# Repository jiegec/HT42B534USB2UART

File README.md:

# HT42B534 USB 2 UART Board

A simple USB to UART board. Designed with KiCad. Manufactured and tested.

## How to use

1. Plug USB to your PC
2. Wire VIO to either V33O(3.3V) or VDD(5V)
3. Connect TX, RX & GND (optionally VIO) to other devices

The voltage of RX/TX should match VIO.

## Bill of Materials

```csv
Reference, Value, Footprint, Datasheet, Product
"U1","HT42B534_8SOP","Package_SO:SOP-8_3.9x4.9mm_P1.27mm","https://www.holtek.com/documents/10179/116711/HT42B534-xv110.pdf","https://item.szlcsc.com/504007.html"
"C1","0.1uF","Capacitor_SMD:C_0603_1608Metric_Pad1.08x0.95mm_HandSolder","~"
"J1","USB_A","Connector_USB:USB_A_CNCTech_1001-011-01101_Horizontal","~","https://item.szlcsc.com/98530.html"
"R2","33","Resistor_SMD:R_0603_1608Metric_Pad0.98x0.95mm_HandSolder","~"
"R1","33","Resistor_SMD:R_0603_1608Metric_Pad0.98x0.95mm_HandSolder","~"
"C6","47pF","Capacitor_SMD:C_0603_1608Metric_Pad1.08x0.95mm_HandSolder","~"
"C7","47pF","Capacitor_SMD:C_0603_1608Metric_Pad1.08x0.95mm_HandSolder","~"
"C3","1uF","Capacitor_SMD:C_0603_1608Metric_Pad1.08x0.95mm_HandSolder","~"
"C2","0.1uF","Capacitor_SMD:C_0603_1608Metric_Pad1.08x0.95mm_HandSolder","~"
"C4","10uF","Capacitor_SMD:C_0603_1608Metric_Pad1.08x0.95mm_HandSolder","~"
"C5","0.1uF","Capacitor_SMD:C_0603_1608Metric_Pad1.08x0.95mm_HandSolder","~"
"R3","330","Resistor_SMD:R_0603_1608Metric_Pad0.98x0.95mm_HandSolder","~"
"D1","LED","Diode_SMD:D_0603_1608Metric_Pad1.05x0.95mm_HandSolder","~"
"J3","Conn_01x03","Connector_PinHeader_2.54mm:PinHeader_1x03_P2.54mm_Vertical","~"
"J2","Conn_01x04","Connector_PinHeader_2.54mm:PinHeader_1x04_P2.54mm_Horizontal","~"
```

## USB Device Info

`lsusb` output:

```shell
$ lsusb
Bus 000 Device 001: ID 04d9:b534 Holtek Semiconductor, Inc. USB TO UART BRIDGE  Serial: 0000
```

System Information:

```
USB TO UART BRIDGE:

  Product ID:	0xb534
  Vendor ID:	0x04d9  (Holtek Semiconductor, Inc.)
  Version:	2.10
  Serial Number:	0000
  Speed:	Up to 12 Mb/s
  Manufacturer:	HOLTEK
  Location ID:	0x00142000 / 12
  Current Available (mA):	500
  Current Required (mA):	100
  Extra Operating Current (mA):	0
```

## License

Copyright 2020-2021 Jiajie Chen

SPDX-License-Identifier: Apache-2.0 WITH SHL-2.1

Licensed under the Solderpad Hardware License v 2.1 (the “License”); you may not use this file except in compliance with the License, or, at your option, the Apache License version 2.0. You may obtain a copy of the License at

https://solderpad.org/licenses/SHL-2.1/

Unless required by applicable law or agreed to in writing, any work distributed under the License is distributed on an “AS IS” BASIS, WITHOUT WARRANTIES OR CONDITIONS OF ANY KIND, either express or implied. See the License for the specific language governing permissions and limitations under the License.

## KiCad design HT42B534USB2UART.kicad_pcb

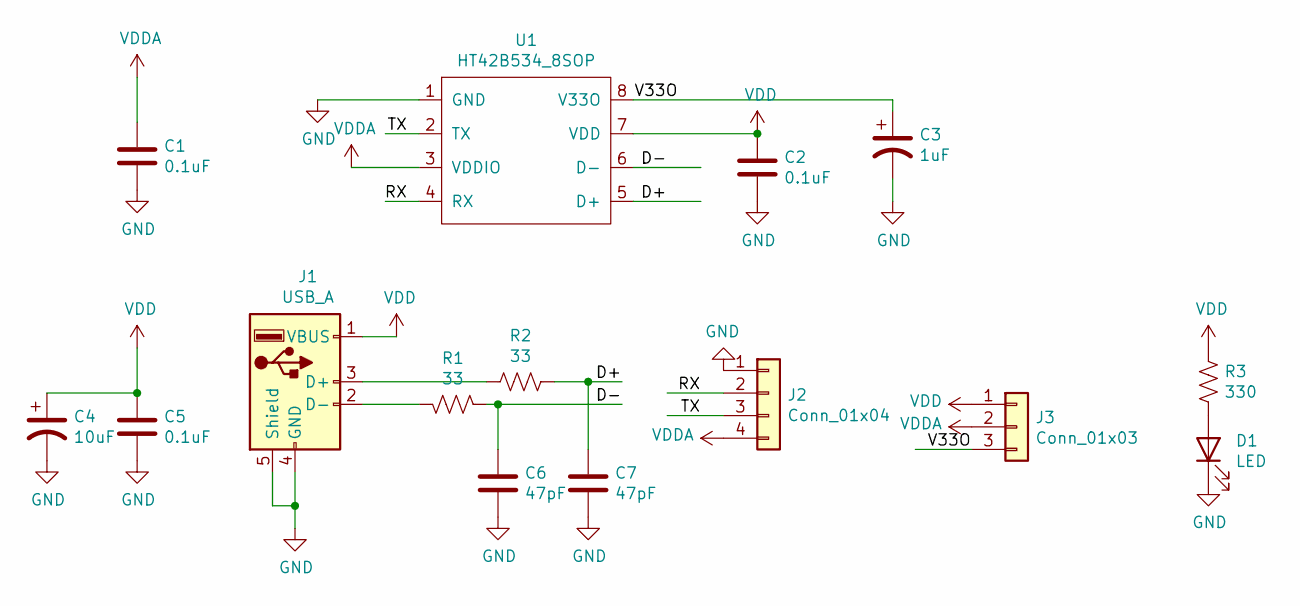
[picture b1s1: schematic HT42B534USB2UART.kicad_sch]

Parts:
C1, C2, C5: 0.1uF; C_0603_1608Metric_Pad1.08x0.95mm_HandSolder
C3: 1uF; C_0603_1608Metric_Pad1.08x0.95mm_HandSolder
C4: 10uF; C_0603_1608Metric_Pad1.08x0.95mm_HandSolder
C6, C7: 47pF; C_0603_1608Metric_Pad1.08x0.95mm_HandSolder
D1: LED; D_0603_1608Metric_Pad1.05x0.95mm_HandSolder
J1: USB_A; USB_A_CNCTech_1001-011-01101_Horizontal
J2: Conn_01x04; PinHeader_1x04_P2.54mm_Horizontal
J3: Conn_01x03; PinHeader_1x03_P2.54mm_Vertical
R1, R2: 33; R_0603_1608Metric_Pad0.98x0.95mm_HandSolder
R3: 330; R_0603_1608Metric_Pad0.98x0.95mm_HandSolder
U1: HT42B534_8SOP; SOP-8_3.9x4.9mm_P1.27mm

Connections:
/D+: C7.1, R2.1, U1.5 (D+)
/D-: C6.1, R1.1, U1.6 (D-)
/RX: J2.2, U1.4 (RX)
/TX: J2.3, U1.2 (TX)
/V33O: C3.1, J3.3, U1.8 (V33O)
GND: C1.2, C2.2, C3.2, C4.2, C5.2, C6.2, C7.2, D1.1 (K), J1.4 (GND), J1.5 (Shield), J2.1, U1.1 (GND)
unnamed: D1.2 (A), R3.2
unnamed: J1.2 (D-), R1.2
unnamed: J1.3 (D+), R2.2
VDD: C2.1, C4.1, C5.1, J1.1 (VBUS), J3.1, R3.1, U1.7 (VDD)
VDDA: C1.1, J2.4, J3.2, U1.3 (VDDIO)

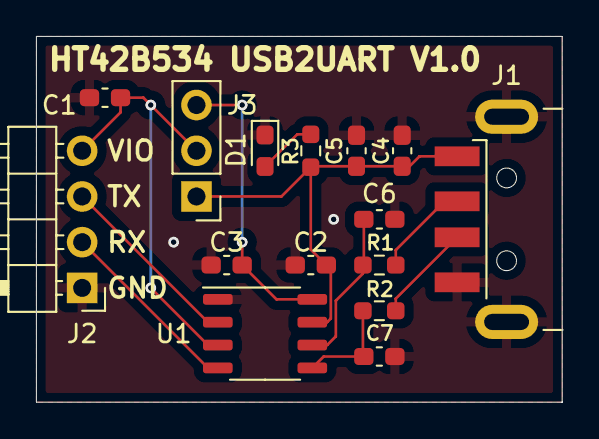
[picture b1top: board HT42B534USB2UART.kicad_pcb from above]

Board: 2 copper layers, 29.2 x 20.3 mm, 15 parts (0 on the bottom side), 11 nets.

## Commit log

2020-12-27 Initial version of HT42B534 USB to UART board
2020-12-28 Setup board parameters(track width, via size etc) and use filled Cu layers
2020-12-28 Add slik text
2020-12-28 Add a conn01x03 for voltage selection
2020-12-28 Move gerber files to subdir
2020-12-28 Add License and README
2020-12-28 Add missing drill file
2021-01-02 Use custom symbol library
2021-01-03 Add some info to README
2021-01-03 Add License to README
2021-01-03 Add rendered images
2021-01-03 Add szlcsc url to purchase
2021-01-03 Minor update
2021-01-03 Fix extra whitespace
2021-12-29 Kicad 6.0
2021-12-29 Make text smaller and regenerate gerber
2021-12-29 Sync with github .gitignore
2022-04-21 Add usage to README
2023-04-17 Fix README format
2023-05-04 Bump kicad version
